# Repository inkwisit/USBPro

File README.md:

# USBPro
FT2232H based USB engine for rapid USB development.

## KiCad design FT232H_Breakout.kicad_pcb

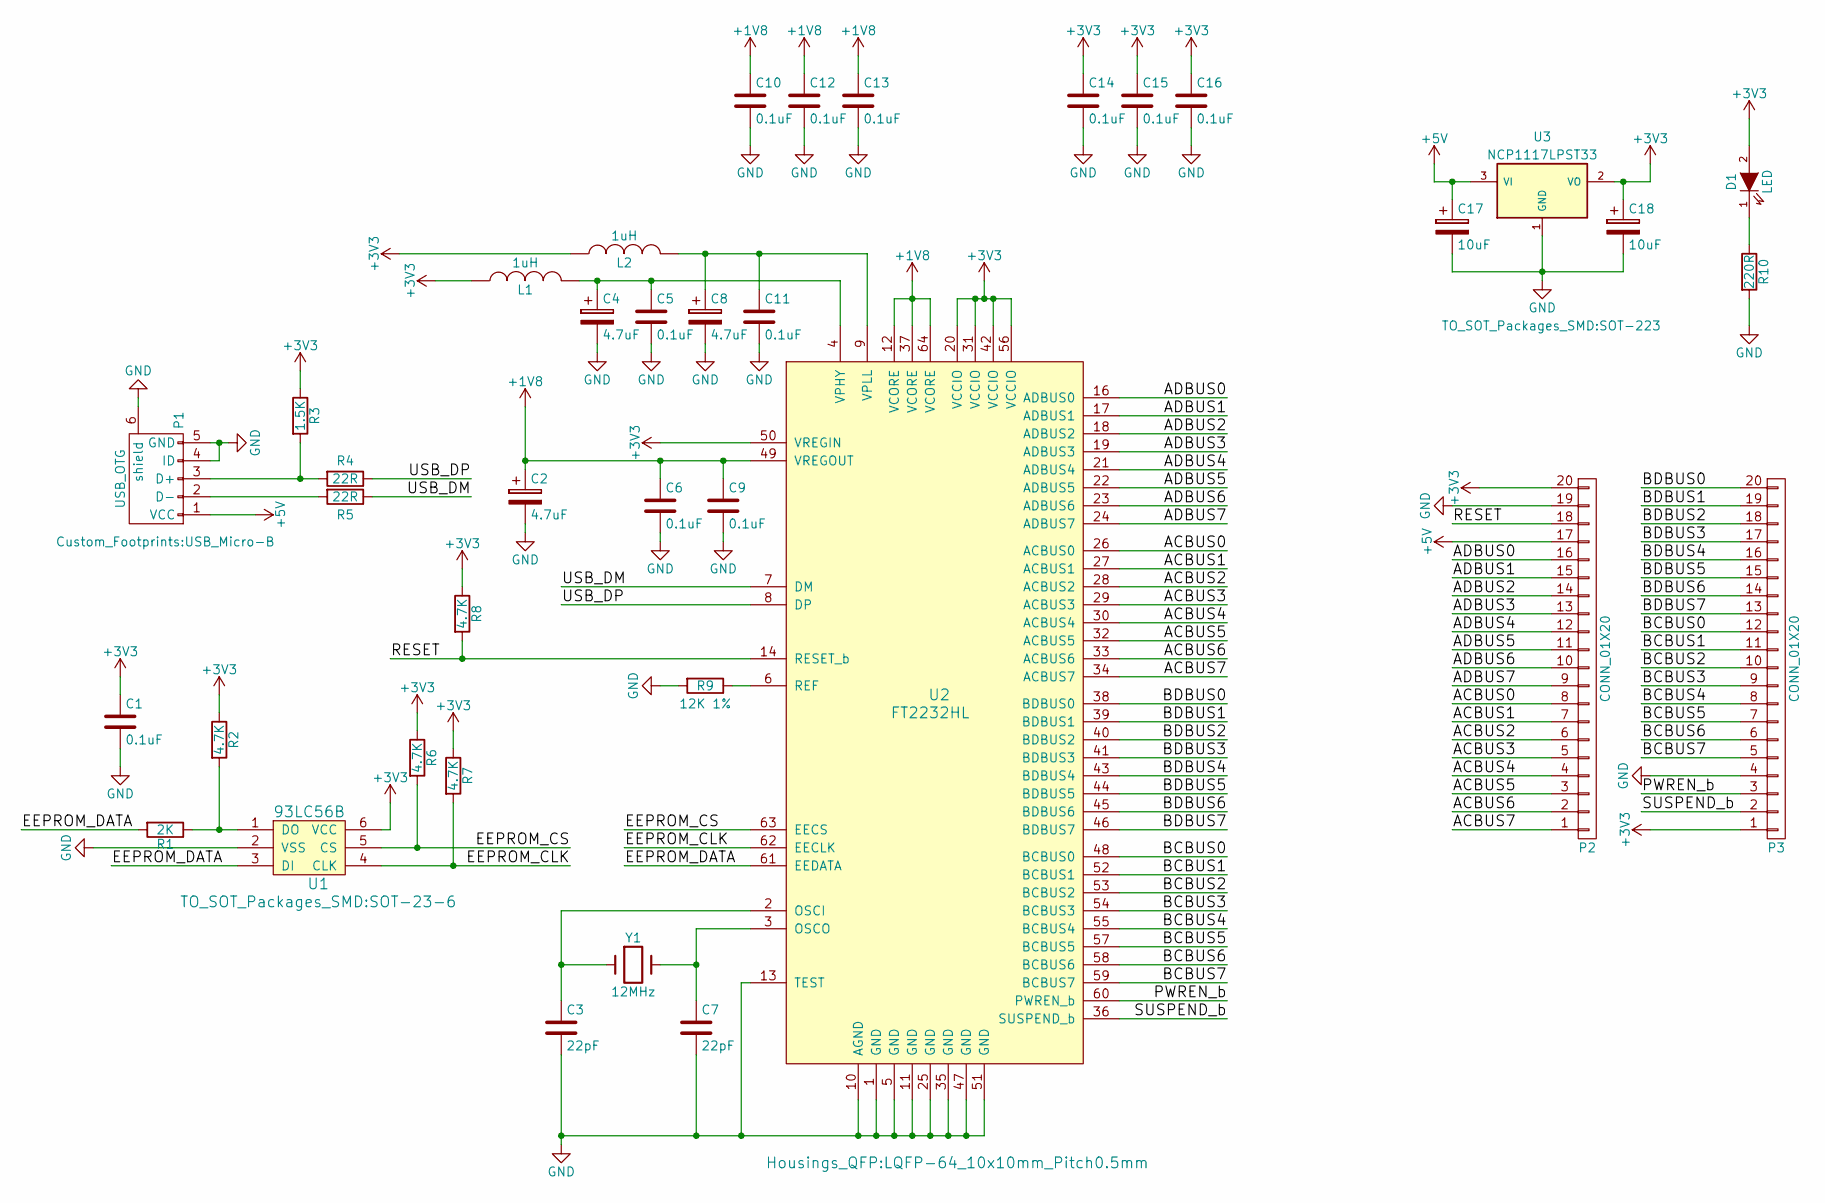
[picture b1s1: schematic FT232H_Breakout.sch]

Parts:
C1, C5, C6, C9, C10, C11, C12, C13, C14, C15, C16: 0.1uF; C_0805_HandSoldering
C2, C4, C8: 4.7uF; TantalC_SizeS_EIA-3216
C3, C7: 22pF; C_0805_HandSoldering
C17, C18: 10uF; TantalC_SizeS_EIA-3216
D1: LED; LED_0805
L1, L2: 1uH; Inductor_0805
P1: USB_OTG; USB_Micro-B
P2, P3: CONN_01X20; Pin_Header_Straight_1x20_without_3D
R1: 2K; R_0805_HandSoldering
R2, R6, R7, R8: 4.7K; R_0805_HandSoldering
R3: 1.5K; R_0805_HandSoldering
R4, R5: 22R; R_0805_HandSoldering
R9: 12K 1%; R_0805_HandSoldering
R10: 220R; R_0805_HandSoldering
U1: 93LC56B; SOT-23-6
U2: FT2232HL; LQFP-64_10x10mm_Pitch0.5mm
U3: NCP1117LPST33; SOT-223
Y1: 12MHz; Q_49U3HMS

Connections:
+1V8: C2.1, C6.1, C9.1, C10.1, C12.1, C13.1, U2.12 (VCORE), U2.37 (VCORE), U2.49 (VREGOUT), U2.64 (VCORE)
+3V3: C1.1, C14.1, C15.1, C16.1, C18.1, D1.2 (A), L1.1, L2.1, P2.20, P3.1, R2.1, R3.1, R6.1, R7.1, R8.1, U1.6 (VCC), U2.20 (VCCIO), U2.31 (VCCIO), U2.42 (VCCIO), U2.50 (VREGIN), U2.56 (VCCIO), U3.2 (VO)
+5V: C17.1, P1.1 (VCC), P2.17, U3.3 (VI)
/ACBUS0: P2.8, U2.26 (ACBUS0)
/ACBUS1: P2.7, U2.27 (ACBUS1)
/ACBUS2: P2.6, U2.28 (ACBUS2)
/ACBUS3: P2.5, U2.29 (ACBUS3)
/ACBUS4: P2.4, U2.30 (ACBUS4)
/ACBUS5: P2.3, U2.32 (ACBUS5)
/ACBUS6: P2.2, U2.33 (ACBUS6)
/ACBUS7: P2.1, U2.34 (ACBUS7)
/ADBUS0: P2.16, U2.16 (ADBUS0)
/ADBUS1: P2.15, U2.17 (ADBUS1)
/ADBUS2: P2.14, U2.18 (ADBUS2)
/ADBUS3: P2.13, U2.19 (ADBUS3)
/ADBUS4: P2.12, U2.21 (ADBUS4)
/ADBUS5: P2.11, U2.22 (ADBUS5)
/ADBUS6: P2.10, U2.23 (ADBUS6)
/ADBUS7: P2.9, U2.24 (ADBUS7)
/BCBUS0: P3.12, U2.48 (BCBUS0)
/BCBUS1: P3.11, U2.52 (BCBUS1)
/BCBUS2: P3.10, U2.53 (BCBUS2)
/BCBUS3: P3.9, U2.54 (BCBUS3)
/BCBUS4: P3.8, U2.55 (BCBUS4)
/BCBUS5: P3.7, U2.57 (BCBUS5)
/BCBUS6: P3.6, U2.58 (BCBUS6)
/BCBUS7: P3.5, U2.59 (BCBUS7)
/BDBUS0: P3.20, U2.38 (BDBUS0)
/BDBUS1: P3.19, U2.39 (BDBUS1)
/BDBUS2: P3.18, U2.40 (BDBUS2)
/BDBUS3: P3.17, U2.41 (BDBUS3)
/BDBUS4: P3.16, U2.43 (BDBUS4)
/BDBUS5: P3.15, U2.44 (BDBUS5)
/BDBUS6: P3.14, U2.45 (BDBUS6)
/BDBUS7: P3.13, U2.46 (BDBUS7)
/EEPROM_CLK: R7.2, U1.4 (CLK), U2.62 (EECLK)
/EEPROM_CS: R6.2, U1.5 (CS), U2.63 (EECS)
/EEPROM_DATA: R1.2, U1.3 (DI), U2.61 (EEDATA)
/PWREN_b: P3.3, U2.60 (PWREN_b)
/RESET: P2.18, R8.2, U2.14 (RESET_b)
/SUSPEND_b: P3.2, U2.36 (SUSPEND_b)
/USB_DM: R5.1, U2.7 (DM)
/USB_DP: R4.1, U2.8 (DP)
GND: C1.2, C2.2, C3.2, C4.2, C5.2, C6.2, C7.2, C8.2, C9.2, C10.2, C11.2, C12.2, C13.2, C14.2, C15.2, C16.2, C17.2, C18.2, P1.4 (ID), P1.5 (GND), P1.6 (shield), P2.19, P3.4, R9.2, R10.2, U1.2 (VSS), U2.1 (GND), U2.5 (GND), U2.10 (AGND), U2.11 (GND), U2.13 (TEST), U2.25 (GND), U2.35 (GND), U2.47 (GND), U2.51 (GND), U3.1 (GND)
unnamed: C3.1, U2.2 (OSCI), Y1.1
unnamed: C4.1, C5.1, L1.2, U2.4 (VPHY)
unnamed: C7.1, U2.3 (OSCO), Y1.2
unnamed: C8.1, C11.1, L2.2, U2.9 (VPLL)
unnamed: D1.1 (K), R10.1
unnamed: P1.2 (D-), R5.2
unnamed: P1.3 (D+), R3.2, R4.2
unnamed: R1.1, R2.2, U1.1 (DO)
unnamed: R9.1, U2.6 (REF)

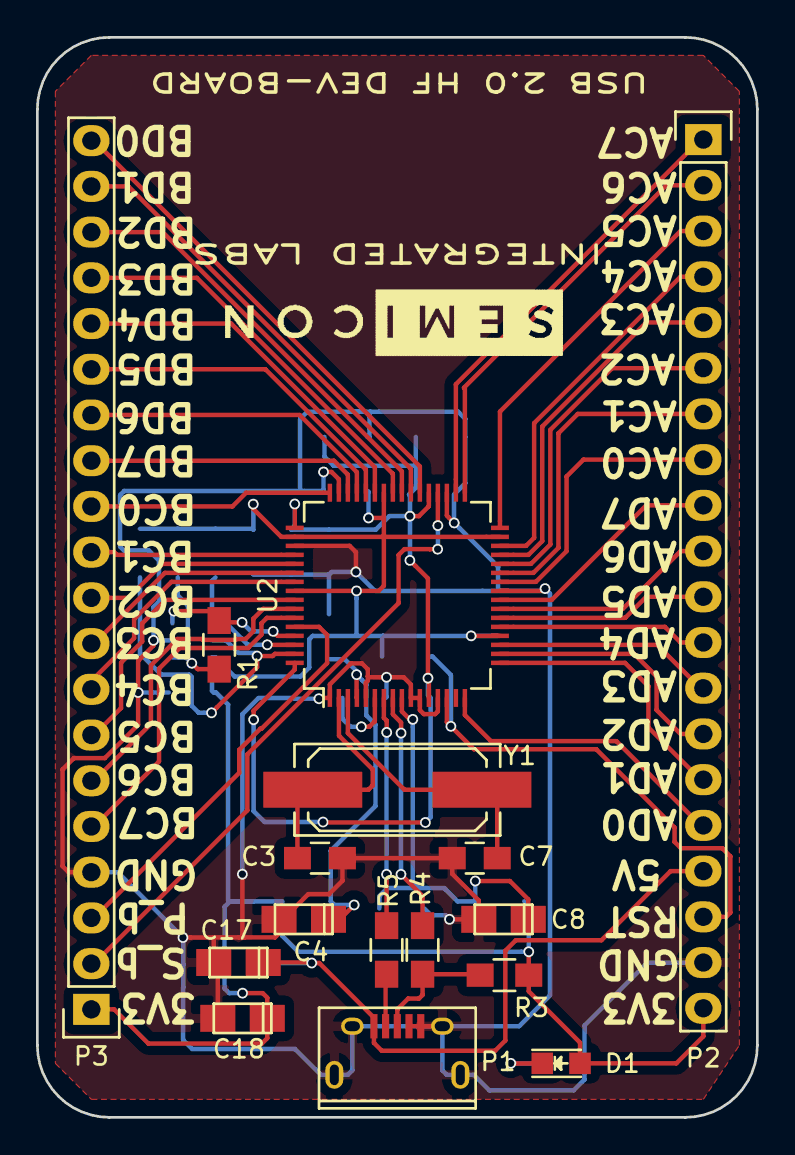
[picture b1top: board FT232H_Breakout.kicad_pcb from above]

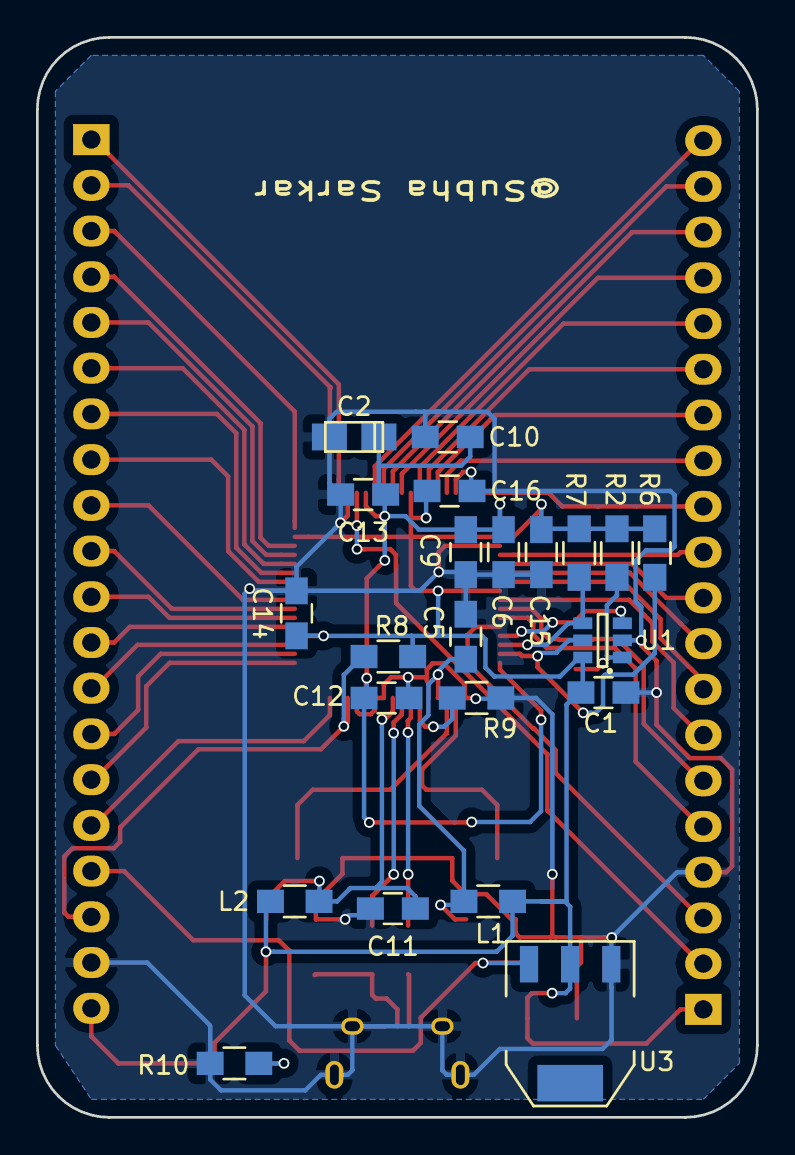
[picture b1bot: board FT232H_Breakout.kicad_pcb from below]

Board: 2 copper layers, 40.0 x 60.0 mm, 39 parts (22 on the bottom side), 53 nets.

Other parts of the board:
LOGO: LOGO_19mm

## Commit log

2018-01-01 Initial commit of USBpro
2018-01-01 License added
